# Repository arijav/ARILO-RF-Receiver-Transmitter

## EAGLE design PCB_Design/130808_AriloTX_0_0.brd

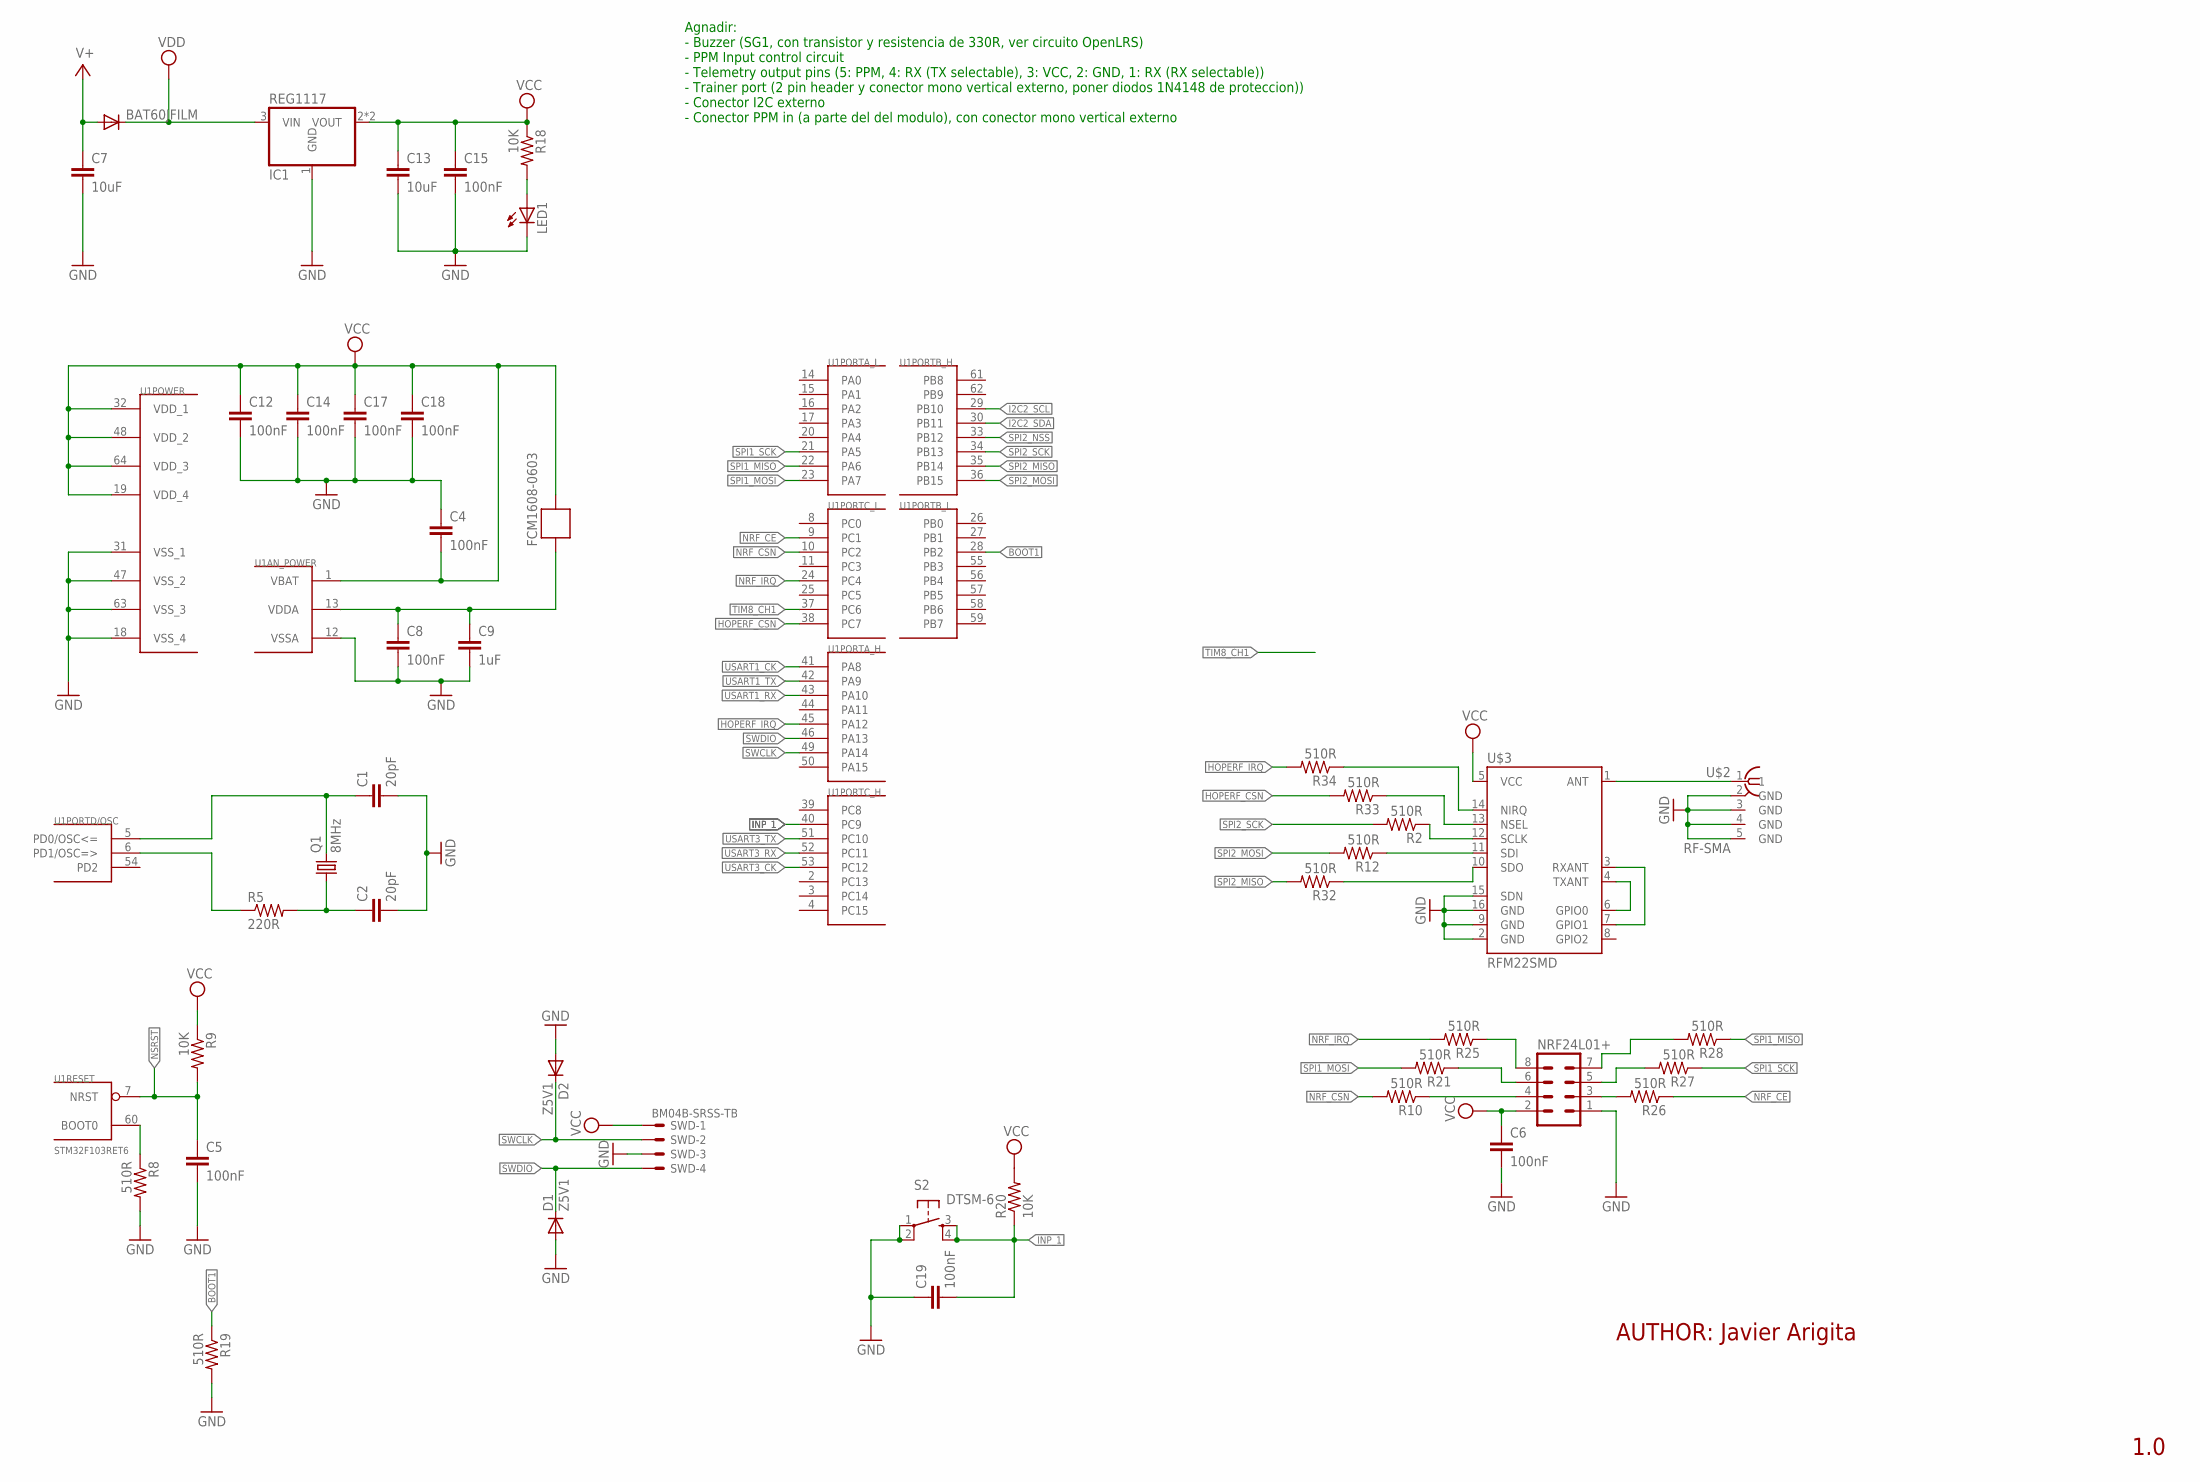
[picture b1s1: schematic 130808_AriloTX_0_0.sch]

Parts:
BAT60JFILM: DIODE-SOD323-R; SOD323-R
C1, C2: 20pF; C0805
C4, C5, C6, C8, C12, C14, C15, C17, C18, C19: 100nF; C0805
C7, C13: 10uF; C3216
C9: 1uF; C3216
D1, D2: Z5V1; SOD323-R
FCM1608-0603: FERRITE-BEAD; R0603
IC1: REG1117; SOT223
LED1: LED0805; CHIPLED_0805
NRF24L01+: MA04-2
Q1: 8MHz; SM49
R2, R8, R10, R12, R19, R21, R25, R26, R27, R28, R32, R33, R34: 510R; R0805
R5: 220R; R0805
R9, R18, R20: 10K; R0805
S2: DTSM-6
SWD: BM04B-SRSS-TB
U1: STM32F103RET6; TQFP64
U$2: RF-SMA; BU-SMA-H
U$3: RFM22SMD; RFM22-XXX-S2

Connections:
BOOT1: R19.1, U1.28 (PB2)
GND: C1.2, C2.2, C4.1, C5.2, C6.2, C7.2, C8.2, C9.2, C12.2, C13.2, C14.2, C15.2, C17.2, C18.2, C19.1, D1.A, D2.A, IC1.1 (GND), LED1.C, NRF24L01+.1, R8.2, R19.2, S2.1, S2.2, SWD.3, U1.12 (VSSA), U1.18 (VSS_4), U1.31 (VSS_1), U1.47 (VSS_2), U1.63 (VSS_3), U$2.2 (GND), U$2.3 (GND), U$2.4 (GND), U$2.5 (GND), U$3.2 (GND), U$3.9 (GND), U$3.15 (SDN), U$3.16 (GND)
HOPERF_CSN: R33.2, U1.38 (PC7)
HOPERF_IRQ: R34.2, U1.45 (PA12)
I2C2_SCL: U1.29 (PB10)
I2C2_SDA: U1.30 (PB11)
INP_1: C19.2, R20.1, S2.3, S2.4, U1.40 (PC9)
unnamed: C1.1, Q1.2, U1.5 (PD0/OSC<=)
unnamed: R5.1, U1.6 (PD1/OSC=>)
unnamed: C2.1, Q1.1, R5.2
unnamed: R8.1, U1.60 (BOOT0)
unnamed: U$3.3 (RXANT), U$3.7 (GPIO1)
unnamed: U$3.4 (TXANT), U$3.6 (GPIO0)
unnamed: R2.1, U$3.12 (SCLK)
unnamed: R12.1, U$3.11 (SDI)
unnamed: LED1.A, R18.2
unnamed: R32.1, U$3.10 (SDO)
unnamed: C8.1, C9.1, FCM1608-0603.2, U1.13 (VDDA)
unnamed: NRF24L01+.4, R10.1
unnamed: NRF24L01+.3, R26.2
unnamed: U$2.1, U$3.1 (ANT)
unnamed: R34.1, U$3.14 (NIRQ)
unnamed: R33.1, U$3.13 (NSEL)
unnamed: NRF24L01+.5, R27.2
unnamed: NRF24L01+.6, R21.1
unnamed: NRF24L01+.8, R25.1
unnamed: NRF24L01+.7, R28.2
NRF_CE: R26.1, U1.9 (PC1)
NRF_CSN: R10.2, U1.10 (PC2)
NRF_IRQ: R25.2, U1.24 (PC4)
NSRST: C5.1, R9.2, U1.7 (NRST)
SPI1_MISO: R28.1, U1.22 (PA6)
SPI1_MOSI: R21.2, U1.23 (PA7)
SPI1_SCK: R27.1, U1.21 (PA5)
SPI2_MISO: R32.2, U1.35 (PB14)
SPI2_MOSI: R12.2, U1.36 (PB15)
SPI2_NSS: U1.33 (PB12)
SPI2_SCK: R2.2, U1.34 (PB13)
SWCLK: D2.C, SWD.2, U1.49 (PA14)
SWDIO: D1.C, SWD.4, U1.46 (PA13)
TIM8_CH1: U1.37 (PC6)
USART1_CK: U1.41 (PA8)
USART1_RX: U1.43 (PA10)
USART1_TX: U1.42 (PA9)
USART3_CK: U1.53 (PC12)
USART3_RX: U1.52 (PC11)
USART3_TX: U1.51 (PC10)
V+: BAT60JFILM.A, C7.1
VCC: C4.2, C6.1, C12.1, C13.1, C14.1, C15.1, C17.1, C18.1, FCM1608-0603.1, IC1.2 (VOUT), IC1.4 (VOUT), NRF24L01+.2, R9.1, R18.1, R20.2, SWD.1, U1.1 (VBAT), U1.19 (VDD_4), U1.32 (VDD_1), U1.48 (VDD_2), U1.64 (VDD_3), U$3.5 (VCC)
VDD: BAT60JFILM.C, IC1.3 (VIN)

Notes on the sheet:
AUTHOR: Javier Arigita
1.0
Agnadir: - Buzzer (SG1, con transistor y resistencia de 330R, ver circuito OpenLRS) - PPM Input control circuit - Telemetry output pins (5: PPM, 4: RX (TX selectable), 3: VCC, 2: GND, 1: RX (RX selectable)) - Trainer port (2 pin header y conector mono vertical externo, poner diodos 1N4148 de protec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

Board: 2 copper layers, 45 parts (18 on the bottom side), 40 nets, no tracks yet.

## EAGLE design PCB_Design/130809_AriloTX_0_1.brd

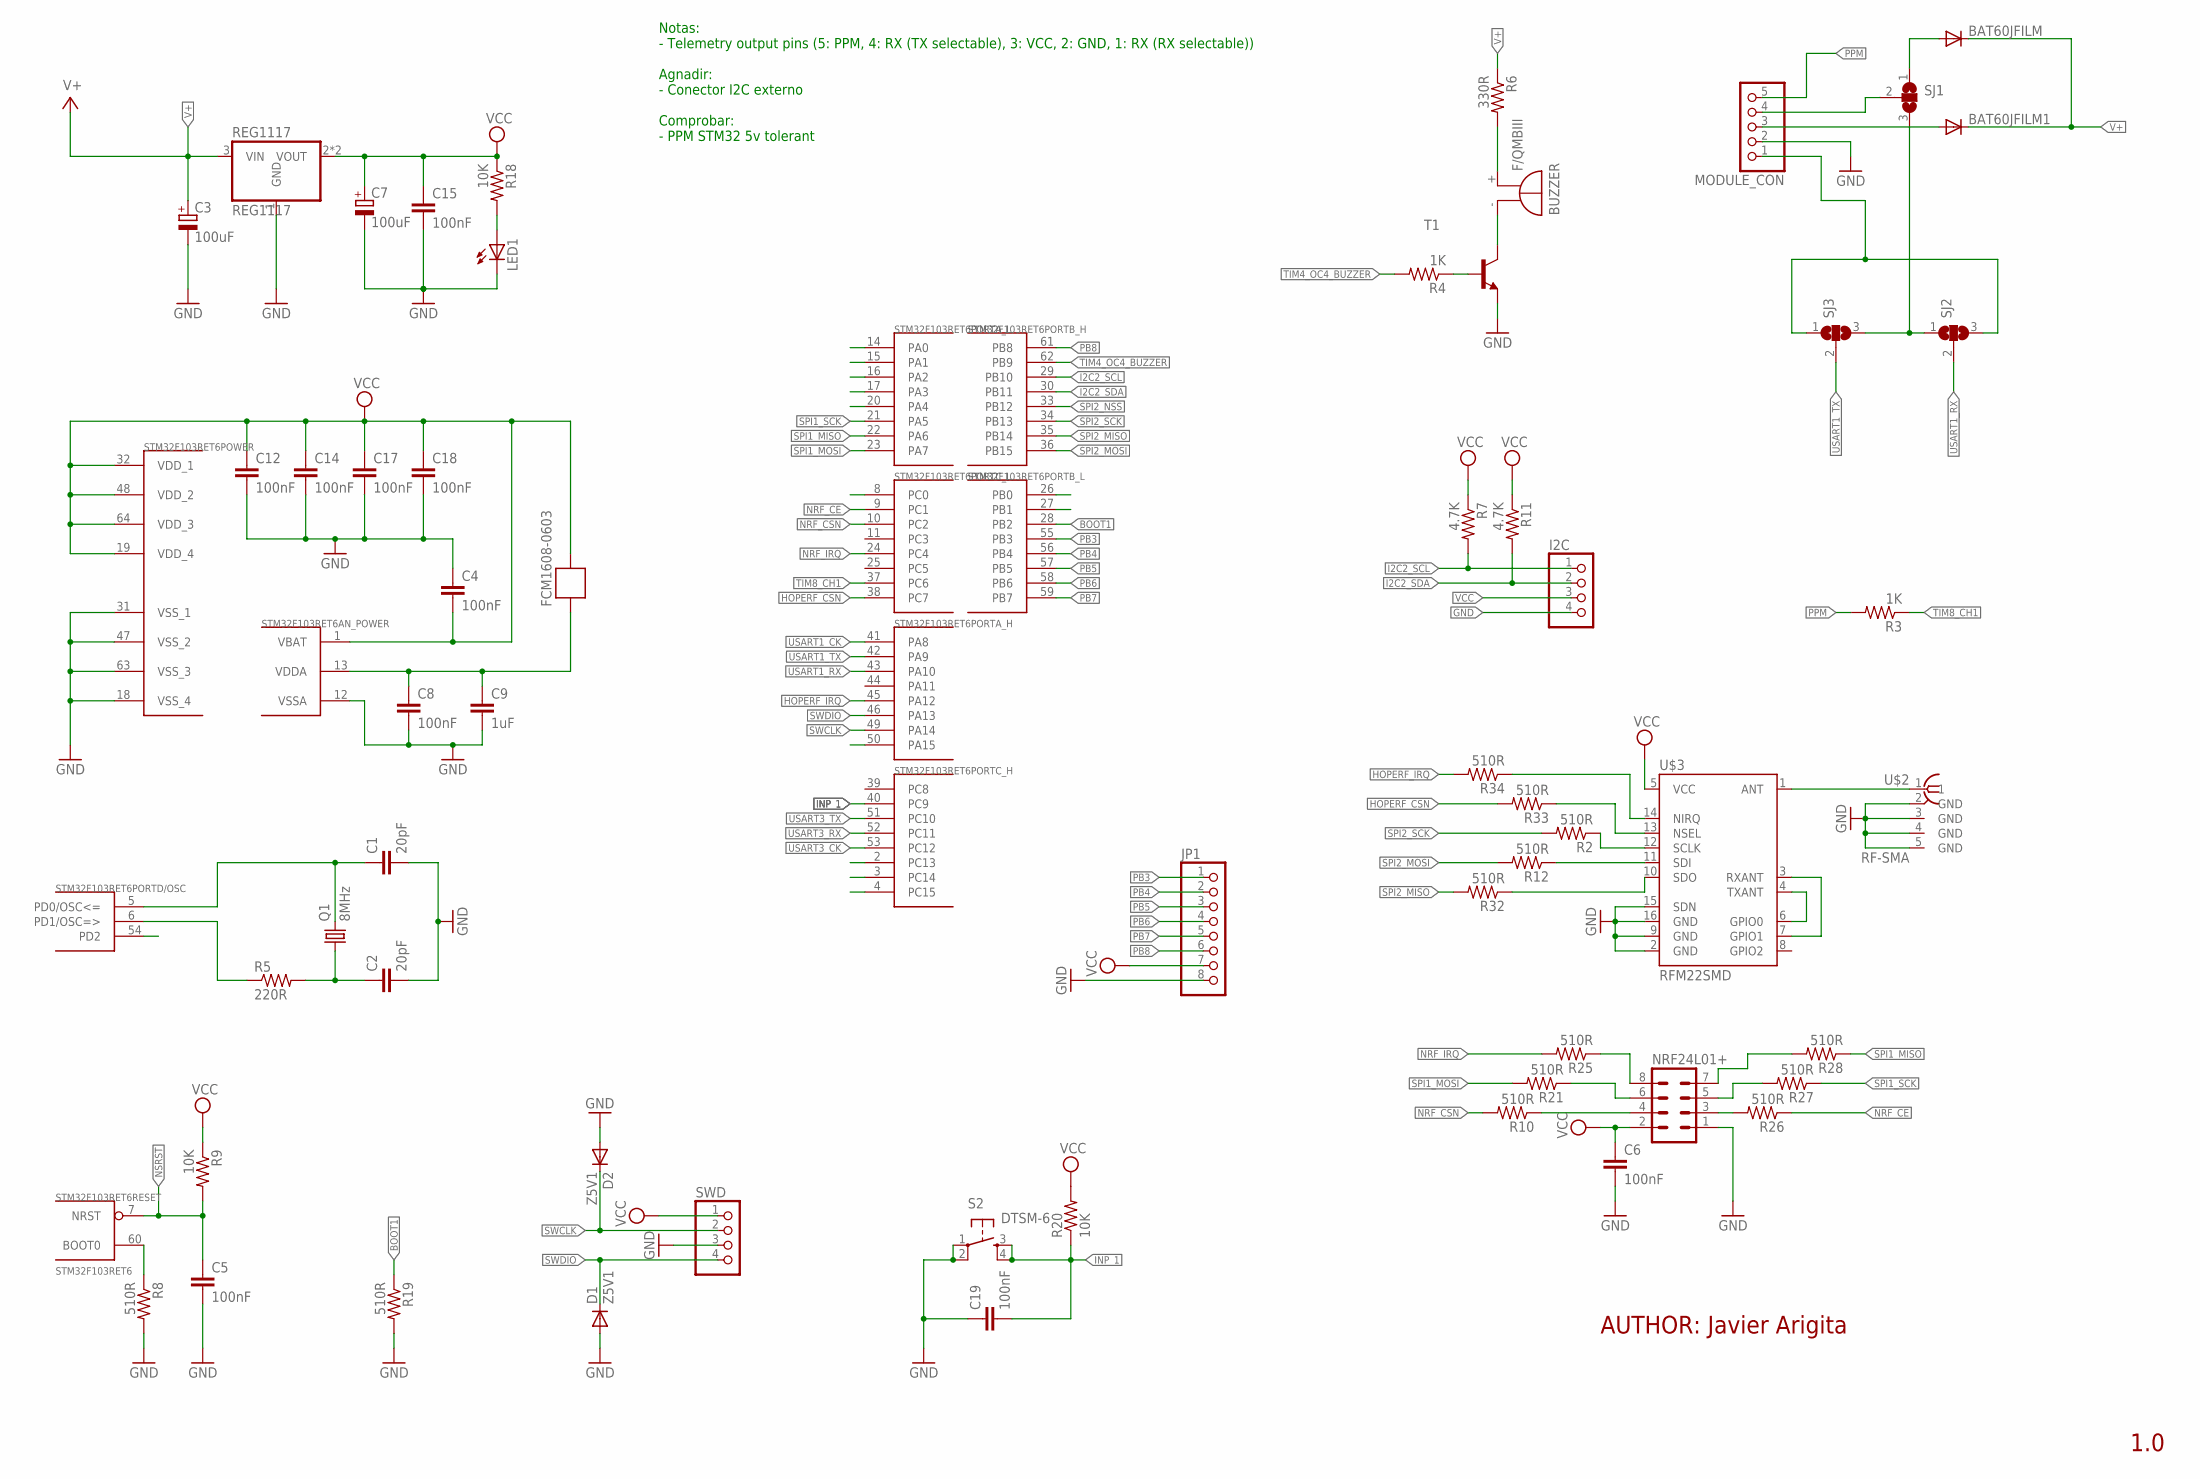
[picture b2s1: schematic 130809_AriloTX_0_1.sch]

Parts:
BAT60JFILM, BAT60JFILM1: DIODE-SOD323-R; SOD323-R
BUZZER: F/QMBIII
C1, C2: 20pF; C0805
C3, C7: 100uF; SMC_B
C4, C5, C6, C8, C12, C14, C15, C17, C18, C19: 100nF; C0805
C9: 1uF; C3216
D1, D2: Z5V1; SOD323-R
FCM1608-0603: FERRITE-BEAD; R0603
I2C: PINHD-1X4; 1X04
JP1: PINHD-1X8; 1X08
LED1: LED0805; CHIPLED_0805
MODULE_CON: PINHD-1X5; 1X05
NRF24L01+: MA04-2
Q1: 8MHz; SM49
R2, R8, R10, R12, R19, R21, R25, R26, R27, R28, R32, R33, R34: 510R; R0805
R3, R4: 1K; R0805
R5: 220R; R0805
R6: 330R; R0805
R7, R11: 4.7K; R0805
R9, R18, R20: 10K; R0805
REG1117: REG1117; SOT223
S2: DTSM-6
SJ1, SJ2, SJ3: SJ2W; SJ_2
STM32F103RET6: STM32F103RET6; TQFP64
SWD: PINHD-1X4; 1X04
T1: BC848-NPN-SOT23-BEC; SOT23-BEC
U$2: RF-SMA; BU-SMA-H
U$3: RFM22SMD; RFM22-XXX-S2

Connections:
BOOT1: R19.1, STM32F103RET6.28 (PB2)
GND: C1.2, C2.2, C3.-, C4.1, C5.2, C6.2, C7.-, C8.2, C9.2, C12.2, C14.2, C15.2, C17.2, C18.2, C19.1, D1.A, D2.A, I2C.4, JP1.8, LED1.C, MODULE_CON.2, NRF24L01+.1, R8.2, R19.2, REG1117.1 (GND), S2.1, S2.2, STM32F103RET6.12 (VSSA), STM32F103RET6.18 (VSS_4), STM32F103RET6.31 (VSS_1), STM32F103RET6.47 (VSS_2), STM32F103RET6.63 (VSS_3), SWD.3, T1.E, U$2.2 (GND), U$2.3 (GND), U$2.4 (GND), U$2.5 (GND), U$3.2 (GND), U$3.9 (GND), U$3.15 (SDN), U$3.16 (GND)
HOPERF_CSN: R33.2, STM32F103RET6.38 (PC7)
HOPERF_IRQ: R34.2, STM32F103RET6.45 (PA12)
I2C2_SCL: I2C.1, R7.2, STM32F103RET6.29 (PB10)
I2C2_SDA: I2C.2, R11.2, STM32F103RET6.30 (PB11)
INP_1: C19.2, R20.1, S2.3, S2.4, STM32F103RET6.40 (PC9)
unnamed: C1.1, Q1.2, STM32F103RET6.5 (PD0/OSC<=)
unnamed: R5.1, STM32F103RET6.6 (PD1/OSC=>)
unnamed: C2.1, Q1.1, R5.2
unnamed: R8.1, STM32F103RET6.60 (BOOT0)
unnamed: U$3.3 (RXANT), U$3.7 (GPIO1)
unnamed: U$3.4 (TXANT), U$3.6 (GPIO0)
unnamed: R2.1, U$3.12 (SCLK)
unnamed: R12.1, U$3.11 (SDI)
unnamed: MODULE_CON.4, SJ1.2
unnamed: LED1.A, R18.2
unnamed: BAT60JFILM.A, SJ1.1
unnamed: R32.1, U$3.10 (SDO)
unnamed: SJ1.3, SJ2.1, SJ3.3
unnamed: BAT60JFILM1.A, MODULE_CON.3
unnamed: MODULE_CON.1, SJ2.3, SJ3.1
unnamed: BUZZER.+ (-), R6.2
unnamed: C8.1, C9.1, FCM1608-0603.2, STM32F103RET6.13 (VDDA)
unnamed: NRF24L01+.4, R10.1
unnamed: NRF24L01+.3, R26.2
unnamed: U$2.1, U$3.1 (ANT)
unnamed: R4.1, T1.B
unnamed: R34.1, U$3.14 (NIRQ)
unnamed: BUZZER.- (+), T1.C
unnamed: R33.1, U$3.13 (NSEL)
unnamed: NRF24L01+.5, R27.2
unnamed: NRF24L01+.6, R21.1
unnamed: NRF24L01+.8, R25.1
unnamed: NRF24L01+.7, R28.2
NRF_CE: R26.1, STM32F103RET6.9 (PC1)
NRF_CSN: R10.2, STM32F103RET6.10 (PC2)
NRF_IRQ: R25.2, STM32F103RET6.24 (PC4)
NSRST: C5.1, R9.2, STM32F103RET6.7 (NRST)
PB3: STM32F103RET6.55 (PB3)
PB4: STM32F103RET6.56 (PB4)
PB5: STM32F103RET6.57 (PB5)
PB6: STM32F103RET6.58 (PB6)
PB7: STM32F103RET6.59 (PB7)
PB8: JP1.6, STM32F103RET6.61 (PB8)
PPM: MODULE_CON.5, R3.2
SPI1_MISO: R28.1, STM32F103RET6.22 (PA6)
SPI1_MOSI: R21.2, STM32F103RET6.23 (PA7)
SPI1_SCK: R27.1, STM32F103RET6.21 (PA5)
SPI2_MISO: R32.2, STM32F103RET6.35 (PB14)
SPI2_MOSI: R12.2, STM32F103RET6.36 (PB15)
SPI2_NSS: STM32F103RET6.33 (PB12)
SPI2_SCK: R2.2, STM32F103RET6.34 (PB13)
SWCLK: D2.C, STM32F103RET6.49 (PA14), SWD.2
SWDIO: D1.C, STM32F103RET6.46 (PA13), SWD.4
TIM4_OC4_BUZZER: R4.2, STM32F103RET6.62 (PB9)
TIM8_CH1: R3.1, STM32F103RET6.37 (PC6)
USART1_CK: STM32F103RET6.41 (PA8)
USART1_RX: SJ2.2, STM32F103RET6.43 (PA10)
USART1_TX: SJ3.2, STM32F103RET6.42 (PA9)
USART3_CK: STM32F103RET6.53 (PC12)
USART3_RX: STM32F103RET6.52 (PC11)
USART3_TX: STM32F103RET6.51 (PC10)
V+: BAT60JFILM.C, BAT60JFILM1.C, C3.+, R6.1, REG1117.3 (VIN)
VCC: C4.2, C6.1, C7.+, C12.1, C14.1, C15.1, C17.1, C18.1, FCM1608-0603.1, I2C.3, JP1.7, NRF24L01+.2, R7.1, R9.1, R11.1, R18.1, R20.2, REG1117.2 (VOUT), REG1117.4 (VOUT), STM32F103RET6.1 (VBAT), STM32F103RET6.19 (VDD_4), STM32F103RET6.32 (VDD_1), STM32F103RET6.48 (VDD_2), STM32F103RET6.64 (VDD_3), SWD.1, U$3.5 (VCC)

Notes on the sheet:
AUTHOR: Javier Arigita
1.0
Notas: - Telemetry output pins (5: PPM, 4: RX (TX selectable), 3: VCC, 2: GND, 1: RX (RX selectable)) Agnadir: - Conector I2C externo Comprobar: - PPM STM32 5v tolerant

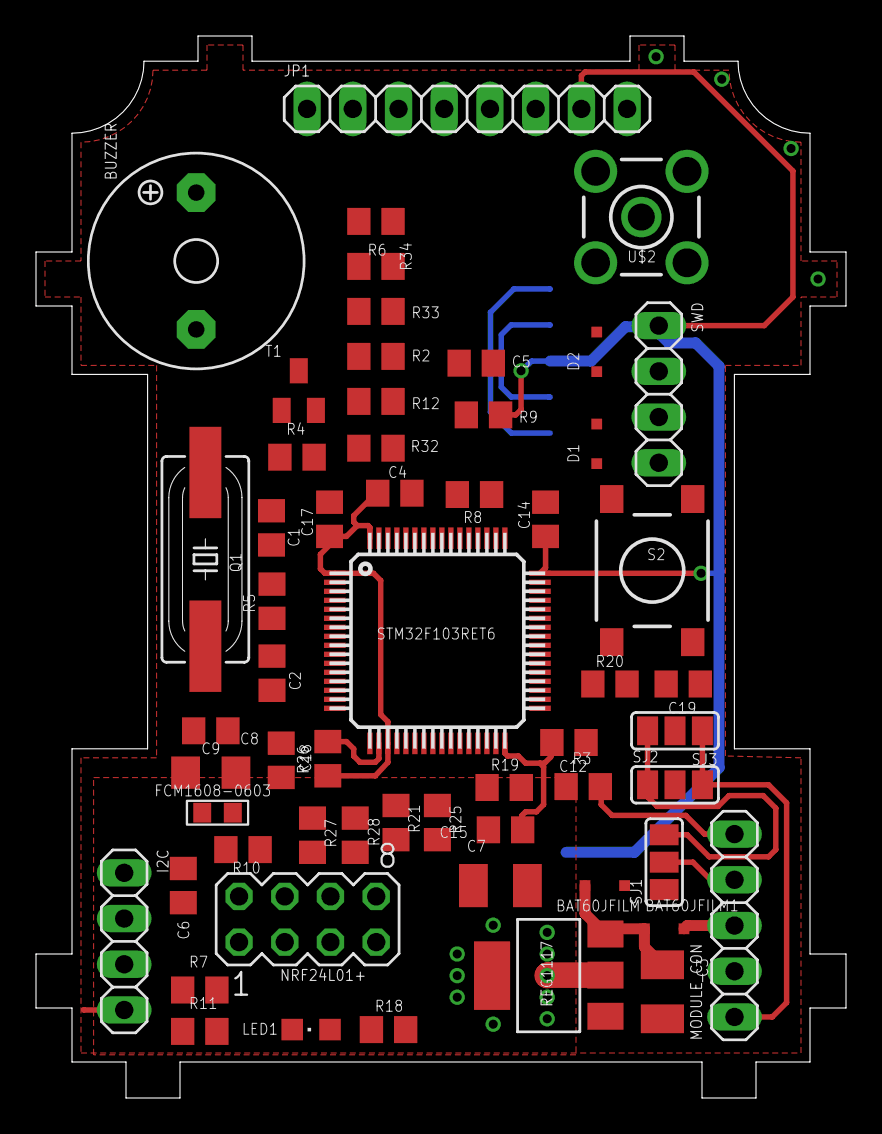
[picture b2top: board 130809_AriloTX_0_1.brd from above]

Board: 2 copper layers, 45.0 x 59.0 mm, 59 parts (1 on the bottom side), 55 nets.

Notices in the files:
parts and their libraries:
SparkFun-RF: Licensing: CC v3.0 Share-Alike You are welcome to use this library for commercial purposes.
